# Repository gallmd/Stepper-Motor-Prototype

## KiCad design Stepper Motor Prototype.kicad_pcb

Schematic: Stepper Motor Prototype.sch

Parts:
C1: 100uF; CP_Radial_D8.0mm_P3.50mm
C2: 0.01uF; C_0603_HandSoldering
C3, C5: 1uF; C_0603_HandSoldering
C4, C6, C7, C8, C9, C17, C18, C19, C20, C21, C22, C23, C24: 0.1uF; C_0603_HandSoldering
C10: 4.7uF; C_0603_HandSoldering
C11, C13: 120uF; CP_Radial_D8.0mm_P3.50mm
C12, C14: 150uF; CP_Radial_D8.0mm_P3.50mm
C15, C16: C; C_0603_HandSoldering
D1: SP0502BAHT; SOT-23
D2: TX_LED; LED_1206_HandSoldering
D3: RX_LED; LED_1206_HandSoldering
D4, D6: D_Schottky; DO-214AB
D5, D7: LED; LED_1206_HandSoldering
J1: USB_B_Micro; USB_Mini-B
J2: Screw_Terminal_01x02; TerminalBlock_bornier-2_P5.08mm
J3: Screw_Terminal_01x04; TerminalBlock_bornier-4_P5.08mm
L1: 100uH; Wurth_SMD_Inductor_7447709101
L2: L; Wurth_SMD_Inductor_7447709101
Q1, Q2, Q3, Q4, Q5, Q6, Q7, Q8: STD20NF06L; TO-252-2
R1, R2, R5, R6: 330R; R_0603_HandSoldering
R3: 4k7; R_0603_HandSoldering
R4: 10k; R_0603_HandSoldering
R7, R8: 0.05R; R_2512
TP1, TP2, TP3, TP4: TestPoint; Test_Point_Keystone_5010-5014_Multipurpose
U1: FT232RL; TSSOP-28_4.4x9.7mm_Pitch0.65mm
U2: ESP8266EX; QFN-32-1EP_5x5mm_Pitch0.5mm
U3: LM2595SX-3.3_NOPB; TO-263-5_TabPin3
U5: LM2595SX-5.0_NOPB; TO-263-5_TabPin3
U6: S25FL512SAGMFIG11; SOIC-16_3.9x9.9mm_Pitch1.27mm
U7: DRV8711; TSSOP-38-1_PowerPad_4.4x9.7mm_Pitch0.5mm
U8: STM32F407VGTx; LQFP-100_14x14mm_Pitch0.5mm
Y1: Crystal_GND24; Crystal_SMD_SeikoEpson_TSX3225-4pin_3.2x2.5mm

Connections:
+3V3: C12.2, C17.2, C18.2, C19.2, C20.2, C21.2, C22.2, C23.2, C24.2, L1.1, R1.2, U3.4, U8.6 (VBAT), U8.11 (VDD), U8.19 (VDD), U8.22 (VDDA), U8.28 (VDD), U8.50 (VDD), U8.75 (VDD), U8.100 (VDD)
+5V: C8.2, C9.2, C10.2, C14.2, D2.2, D3.2, L2.1, R2.2, U1.20, U5.4
+24V: C1.1, C2.1, C3.2, C11.2, C13.2, J2.2, Q1.2, Q4.2, Q5.2, Q8.2, U3.2, U5.2, U7.4
GND: C1.2, C2.2, C4.2, C5.2, C7.2, C8.1, C9.1, C10.1, C11.1, C12.1, C13.1, C14.1, C15.2, C16.2, D1.3, D4.2, D5.1, D6.2, D7.1, J1.5, J1.6, J2.1, R4.1, R7.2, R8.2, TP1.1, TP2.1, TP3.1, TP4.1, U1.7, U1.18, U1.21, U1.25, U1.26, U3.3, U3.5, U5.3, U5.5, U7.5, U7.24, U7.29, U7.33, U7.38, U7.39, U8.10 (VSS), U8.20 (VSSA), U8.27 (VSS), U8.74 (VSS), U8.99 (VSS), Y1.2, Y1.4
unnamed: C3.1, U7.3
unnamed: C4.1, U7.6
unnamed: C5.1, U7.7
unnamed: C6.1, U7.1
unnamed: C6.2, U7.2
unnamed: C7.1, U1.4, U1.17
unnamed: C15.1, U8.12 (PH0), Y1.1
unnamed: C16.1, U8.13 (PH1), Y1.3
unnamed: C17.1, C18.1, C19.1, C20.1, C21.1, C22.1, C23.1, C24.1
unnamed: D1.1, J1.2, U1.16
unnamed: D1.2, J1.3, U1.15
unnamed: D2.1, R5.1
unnamed: D3.1, R6.1
unnamed: D4.1, L1.2, U3.1
unnamed: D5.2, R1.1
unnamed: D6.1, L2.2, U5.1
unnamed: D7.2, R2.1
unnamed: J1.1, R3.2
unnamed: J3.1, Q1.3, Q2.2, U7.37
unnamed: J3.2, Q3.2, Q4.3, U7.30
unnamed: J3.3, Q5.3, Q6.2, U7.28
unnamed: J3.4, Q6.3, Q7.3, R8.1, U7.21, U7.25
unnamed: Q1.1, U7.36
unnamed: Q2.1, U7.35
unnamed: Q2.3, Q3.3, R7.1, U7.34
unnamed: Q3.1, U7.32
unnamed: Q4.1, U7.31
unnamed: Q5.1, U7.27
unnamed: Q6.1, U7.26
unnamed: Q7.1, U7.23
unnamed: Q7.2, Q8.3
unnamed: Q8.1, U7.22
unnamed: R3.1, R4.2, U1.19
unnamed: R5.2, U1.23
unnamed: R6.2, U1.22

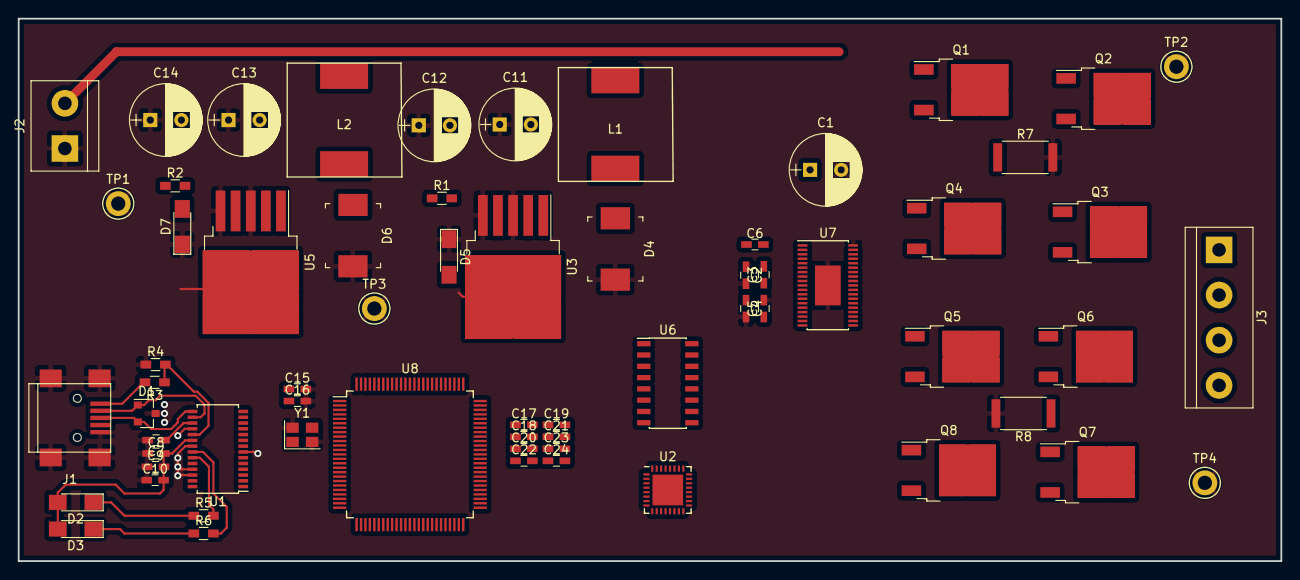
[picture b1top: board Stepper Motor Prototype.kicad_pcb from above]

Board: 2 copper layers, 142.0 x 61.0 mm, 64 parts (0 on the bottom side), 39 nets.

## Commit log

2019-02-09 committing before ripping whole board up. Board will now only contain power seciton and 1 stepper driver
